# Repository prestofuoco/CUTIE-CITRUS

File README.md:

# computational imaging & telemetry for reconnaissance under suborbit
see CUTIE-CITRUS.pdf for schematics, and layout.pdf for PCB layout.

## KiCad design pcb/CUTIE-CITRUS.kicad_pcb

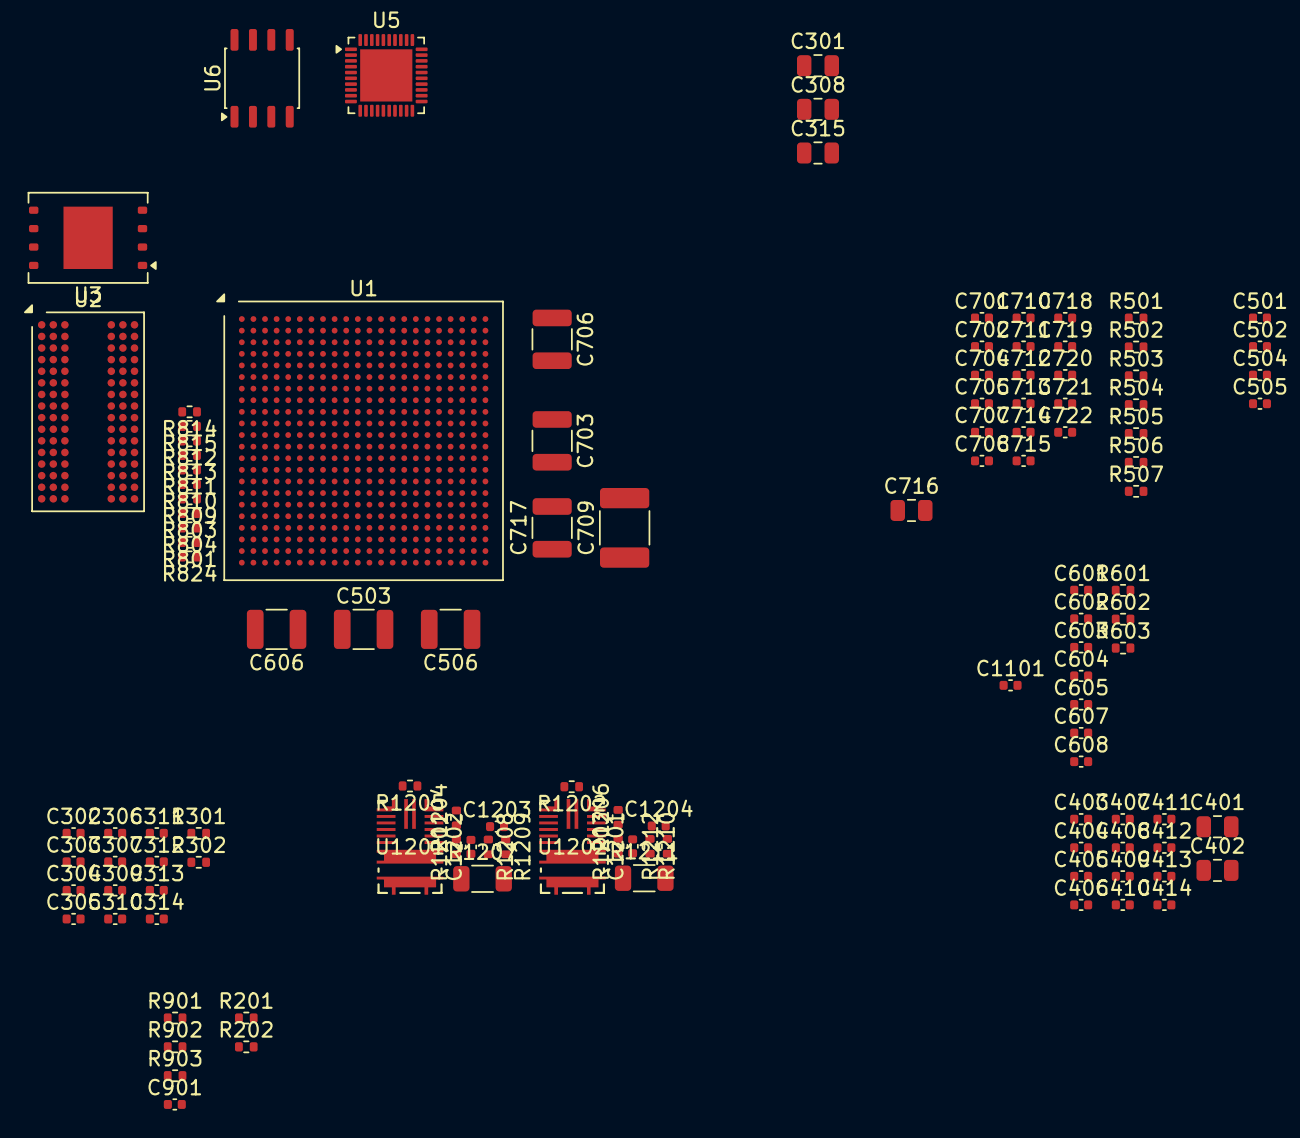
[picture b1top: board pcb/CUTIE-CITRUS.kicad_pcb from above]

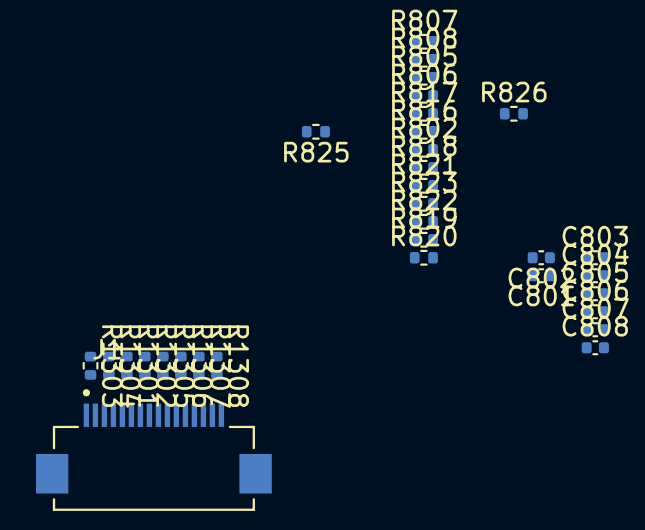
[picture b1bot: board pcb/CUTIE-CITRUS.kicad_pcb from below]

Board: 2 copper layers, 150 parts (32 on the bottom side), 142 nets, no tracks yet.

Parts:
C301, C308, C315, C401, C402, C716: 47uF; C_0805_2012Metric
C302, C303, C309, C310, C403, C404, C405, C406, C502, C505, C605, C702, C705, C710, C711, C718, C720: 4.7uF; C_0402_1005Metric
C304, C305, C306, C307, C311, C312, C313, C314, C407, C408, C409, C410, C411, C412, C413, C414, C501, C504, C601, C602, C603, C604, C701, C704, C707, C708, C712, C713, C714, C715, C719, C721, C722: 470nF; C_0402_1005Metric
C503, C506, C606, C703, C706, C717: 100uF; C_1210_3225Metric
C607, C608, C803, C804, C805, C806, C901, C1101, C1203, C1204: 0.1uF; C_0402_1005Metric
C709: 330uF; C_1812_4532Metric
C801, C802: 47nF; C_0402_1005Metric
C807: 1uF; C_0402_1005Metric
C808: 10uF; C_0402_1005Metric
C1201, C1202: 39pF; C_0402_1005Metric
J1: HIROSE_FH12-16S-0.5SH_55; HIROSE_FH12-16S-0.5SH_55_
R201, R202: 10K 1%; R_0402_1005Metric
R301, R302, R603: 4.7K; R_0402_1005Metric
R501, R1203: 20K; R_0402_1005Metric
R502, R503, R504, R505, R506, R507, R901, R902, R903, R1202, R1205: 10K; R_0402_1005Metric
R601, R602, R825: 100; R_0402_1005Metric
R801, R802, R803, R804, R805, R806, R807, R808, R809, R810, R811, R812, R813, R814, R815, R816, R817, R818, R819, R820, R821, R822, R823, R824, R1301, R1302, R1303, R1304, R1305, R1306, R1307, R1308: 22 1%; R_0402_1005Metric
R826: 240; R_0402_1005Metric
R1201: 37.4K; R_0402_1005Metric
R1204: 5.1K; R_0402_1005Metric
R1206: 30K; R_0402_1005Metric
R1207: 0.003; R_1206_3216Metric
R1208, R1209, R1210, R1212: 10; R_0402_1005Metric
R1211: 0.01; R_1206_3216Metric
U1: XC7Z020CLG484; Xilinx_CLG484_CLG485
U2: MT41K256M16; Micron_FBGA-96_7.5x13.5mm_Layout9x16_P0.8mm
U3: S25FL128SAGNFV003; WSON-8-1EP_8x6mm_P1.27mm_EP3.4x4.3mm
U5: RTL8211F-CG; QFN-40-1EP_5x5mm_P0.4mm_EP3.6x3.6mm
U6: TCAN334; JEITA_SOIC-8_3.9x4.9mm_P1.27mm
U1201, U1202: MPM3650; QFN-24_MPM3650_MNP

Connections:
/Debug Connectors/3V3_Z: J1.15, J1.16
/Debug Connectors/JTAG.TCK: R1308.1, U1.G11 (TCK_0)
/Debug Connectors/JTAG.TDI: R1306.1, U1.H13 (TDI_0)
/Debug Connectors/JTAG.TDO: R1305.1, U1.G14 (TDO_0)
/Debug Connectors/JTAG.TMS: R1307.1, U1.G12 (TMS_0)
/Debug Connectors/UART0.RX: R1304.1, U1.B6 (PS_MIO14_500)
/Debug Connectors/UART0.TX: R1303.1, U1.E6 (PS_MIO15_500)
/PHYs/3V3_Z: C1101.1, U6.3 (VCC), U6.8 (STB)
/PHYs/CAN0.RX: U1.G7 (PS_MIO10_500), U6.1 (TXD)
/PHYs/CAN0.TX: U1.B4 (PS_MIO11_500), U6.4 (RXD)
/PHYs/ETH0.MDCK: U1.D10 (PS_MIO52_501), U5.13 (MDC)
/PHYs/ETH0.MDIO: U1.C12 (PS_MIO53_501), U5.14 (MDIO)
/PHYs/ETH0.RX_CLK: U1.A14 (PS_MIO22_501), U5.27 (RXC)
/PHYs/ETH0.RX_CTL: U1.D7 (PS_MIO27_501), U5.26 (RXCTL)
/PHYs/ETH0.RX_D0: U1.E11 (PS_MIO23_501), U5.25 (RXD0)
/PHYs/ETH0.RX_D1: U1.B7 (PS_MIO24_501), U5.24 (RXD1)
/PHYs/ETH0.RX_D2: U1.F12 (PS_MIO25_501), U5.23 (RXD2)
/PHYs/ETH0.RX_D3: U1.A13 (PS_MIO26_501), U5.22 (RXD3)
/PHYs/ETH0.TX_CLK: U1.D6 (PS_MIO16_501), U5.20 (TXC)
/PHYs/ETH0.TX_CTL: U1.F11 (PS_MIO21_501), U5.19 (TXCTL)
/PHYs/ETH0.TX_D0: U1.E9 (PS_MIO17_501), U5.18 (TXD0)
/PHYs/ETH0.TX_D1: U1.A7 (PS_MIO18_501), U5.17 (TXD1)
/PHYs/ETH0.TX_D2: U1.E10 (PS_MIO19_501), U5.16 (TXD2)
/PHYs/ETH0.TX_D3: U1.A8 (PS_MIO20_501), U5.15 (TXD3)
/Power Supply/1V0: R1211.2, R1212.2
/Power Supply/1V0_P: C1201.1, R1203.1, R1210.2, R1211.1, U1202.9 (OUT), U1202.10 (OUT), U1202.11 (OUT), U1202.12 (OUT)
/Power Supply/1V0_PG: R1202.1, U1202.20 (PG), U1202.21 (PG)
/Power Supply/1V0_SENS_N: C1204.2, R1212.1
/Power Supply/1V0_SENS_P: C1204.1, R1210.1
/Power Supply/5V0: R1207.2, R1209.2, U1202.22 (VIN)
/Power Supply/5V0_P: C1202.1, R1201.1, R1207.1, R1208.2, U1201.9 (OUT), U1201.10 (OUT), U1201.11 (OUT), U1201.12 (OUT)
/Power Supply/5V0_PG: R1205.1, U1201.20 (PG), U1201.21 (PG), U1202.16 (EN)
/Power Supply/5V0_SENS_N: C1203.2, R1209.1
/Power Supply/5V0_SENS_P: C1203.1, R1208.1
/Power Supply/VBUS: U1201.16 (EN), U1201.22 (VIN)
/SoC/1V8_Z: C704.2, C705.2, C706.2, C716.2, C720.2, C721.2, C722.2, U1.A10 (VCCO_MIO1_501), U1.B13 (VCCO_MIO1_501), U1.D9 (VCCO_MIO1_501), U1.E12 (VCCO_MIO1_501), U1.K9 (VCCPAUX), U1.K11 (VCCADC_0), U1.L10 (VCCAUX), U1.M9 (VCCPAUX), U1.N10 (VCCAUX), U1.P9 (VCCPAUX), U1.P11 (VCCAUX), U1.R10 (VCCAUX), U1.T9 (VCCPAUX)
/SoC/1V35_DDR: C606.2, C803.2, C804.2, C805.2, C806.2, C807.2, C808.2, R201.1, R601.1, U1.E2 (VCCO_DDR_502), U1.F5 (VCCO_DDR_502), U1.H1 (VCCO_DDR_502), U1.J4 (VCCO_DDR_502), U1.K7 (VCCO_DDR_502), U1.M3 (VCCO_DDR_502), U1.N6 (VCCO_DDR_502), U1.R2 (VCCO_DDR_502), U1.V1 (VCCO_DDR_502), U2.A1 (V_{DDQ}), U2.A8 (V_{DDQ}), U2.B2 (V_{DD}), U2.C1 (V_{DDQ}), U2.C9 (V_{DDQ}), U2.D2 (V_{DDQ}), U2.D9 (V_{DD}), U2.E9 (V_{DDQ}), U2.F1 (V_{DDQ}), U2.G7 (V_{DD}), U2.H2 (V_{DDQ}), U2.H9 (V_{DDQ}), U2.K2 (V_{DD}), U2.K8 (V_{DD}), U2.N1 (V_{DD}), U2.N9 (V_{DD}), U2.R1 (V_{DD}), U2.R9 (V_{DD})
/SoC/2V5_Z: C301.2, C302.2, C303.2, C304.2, C305.2, C306.2, C307.2, U1.AA10 (VCCO_13), U1.AB3 (VCCO_13), U1.T5 (VCCO_13), U1.U8 (VCCO_13), U1.V11 (VCCO_13), U1.W4 (VCCO_13), U1.Y7 (VCCO_13)
/SoC/3V3_Z: C308.2, C309.2, C310.2, C311.2, C312.2, C313.2, C314.2, C315.2, C501.2, C502.2, C503.2, R301.1, R302.1, R501.1, R502.1, R503.2, U1.AA20 (VCCO_33), U1.AB13 (VCCO_33), U1.B3 (VCCO_MIO0_500), U1.C6 (VCCO_MIO0_500), U1.R12 (VCCO_0), U1.T7 (RSVDVCC1), U1.T8 (RSVDVCC2), U1.T10 (RSVDVCC3), U1.T13 (CFGBVS_0), U1.U18 (VCCO_33), U1.V21 (VCCO_33), U1.W14 (VCCO_33), U1.Y17 (VCCO_33)
/SoC/DRAM/0V675_REF: C801.2, C802.2, R201.2, R202.1, U1.H7 (PS_DDR_VREF0_502), U1.P7 (PS_DDR_VREF1_502), U2.H1 (V_{REFDQ}), U2.M8 (V_{REFCA})
/SoC/DRAM/DDR_A0: R801.1, U1.M4 (PS_DDR_A0_502)
/SoC/DRAM/DDR_A0_T: R801.2, U2.N3 (A0)
/SoC/DRAM/DDR_A1: R802.1, U1.M5 (PS_DDR_A1_502)
/SoC/DRAM/DDR_A1_T: R802.2, U2.P7 (A1)
/SoC/DRAM/DDR_A2: R803.1, U1.K4 (PS_DDR_A2_502)
/SoC/DRAM/DDR_A2_T: R803.2, U2.P3 (A2)
/SoC/DRAM/DDR_A3: R804.1, U1.L4 (PS_DDR_A3_502)
/SoC/DRAM/DDR_A3_T: R804.2, U2.N2 (A3)
/SoC/DRAM/DDR_A4: R805.1, U1.K6 (PS_DDR_A4_502)
/SoC/DRAM/DDR_A4_T: R805.2, U2.P8 (A4)
/SoC/DRAM/DDR_A5: R806.1, U1.K5 (PS_DDR_A5_502)
/SoC/DRAM/DDR_A5_T: R806.2, U2.P2 (A5)
/SoC/DRAM/DDR_A6: R807.1, U1.J7 (PS_DDR_A6_502)
/SoC/DRAM/DDR_A6_T: R807.2, U2.R8 (A6)
/SoC/DRAM/DDR_A7: R808.1, U1.J6 (PS_DDR_A7_502)
/SoC/DRAM/DDR_A7_T: R808.2, U2.R2 (A7)
/SoC/DRAM/DDR_A8: R809.1, U1.J5 (PS_DDR_A8_502)
/SoC/DRAM/DDR_A8_T: R809.2, U2.T8 (A8)
/SoC/DRAM/DDR_A9: R810.1, U1.H5 (PS_DDR_A9_502)
/SoC/DRAM/DDR_A9_T: R810.2, U2.R3 (A9)
/SoC/DRAM/DDR_A10: R811.1, U1.J3 (PS_DDR_A10_502)
/SoC/DRAM/DDR_A10_T: R811.2, U2.L7 (A10/AP)
/SoC/DRAM/DDR_A11: R812.1, U1.G5 (PS_DDR_A11_502)
/SoC/DRAM/DDR_A11_T: R812.2, U2.R7 (A11)
/SoC/DRAM/DDR_A12: R813.1, U1.H4 (PS_DDR_A12_502)
/SoC/DRAM/DDR_A12_T: R813.2, U2.N7 (A12/~BC)
/SoC/DRAM/DDR_A13: R814.1, U1.F4 (PS_DDR_A13_502)
/SoC/DRAM/DDR_A13_T: R814.2, U2.T3 (A13)
/SoC/DRAM/DDR_A14: R815.1, U1.G4 (PS_DDR_A14_502)
/SoC/DRAM/DDR_A14_T: R815.2, U2.T7 (A14)
/SoC/DRAM/DDR_BA0: R816.1, U1.L7 (PS_DDR_BA0_502)
/SoC/DRAM/DDR_BA0_T: R816.2, U2.M2 (BA0)
/SoC/DRAM/DDR_BA1: R817.1, U1.L6 (PS_DDR_BA1_502)
/SoC/DRAM/DDR_BA1_T: R817.2, U2.N8 (BA1)
/SoC/DRAM/DDR_BA2: R818.1, U1.M6 (PS_DDR_BA2_502)
/SoC/DRAM/DDR_BA2_T: R818.2, U2.M3 (BA2)
/SoC/DRAM/DDR_CAS: R821.1, U1.P3 (PS_DDR_CAS_B_502)
/SoC/DRAM/DDR_CAS_T: R821.2, U2.K3 (~CAS)
/SoC/DRAM/DDR_CKE: R824.1, U1.V3 (PS_DDR_CKE_502)
/SoC/DRAM/DDR_CKE_T: R824.2, U2.K9 (CKE)
/SoC/DRAM/DDR_CK_N: R825.2, U1.N5 (PS_DDR_CKN_502), U2.K7 (~CK)
/SoC/DRAM/DDR_CK_P: R825.1, U1.N4 (PS_DDR_CKP_502), U2.J7 (CK)
/SoC/DRAM/DDR_CS: R819.1, U1.P6 (PS_DDR_CS_B_502)
/SoC/DRAM/DDR_CS_T: R819.2, U2.L2 (~CS)
/SoC/DRAM/DDR_DM0: U1.H3 (PS_DDR_DM1_502), U2.E7 (LDM)
/SoC/DRAM/DDR_DM1: U1.B1 (PS_DDR_DM0_502), U2.D3 (UDM)
/SoC/DRAM/DDR_DQ0: U1.G2 (PS_DDR_DQ8_502), U2.E3 (DQ0)
/SoC/DRAM/DDR_DQ1: U1.G1 (PS_DDR_DQ9_502), U2.F7 (DQ1)
/SoC/DRAM/DDR_DQ2: U1.L1 (PS_DDR_DQ10_502), U2.F2 (DQ2)
/SoC/DRAM/DDR_DQ3: U1.L2 (PS_DDR_DQ11_502), U2.F8 (DQ3)
/SoC/DRAM/DDR_DQ4: U1.L3 (PS_DDR_DQ12_502), U2.H3 (DQ4)
/SoC/DRAM/DDR_DQ5: U1.K1 (PS_DDR_DQ13_502), U2.H8 (DQ5)
/SoC/DRAM/DDR_DQ6: U1.J1 (PS_DDR_DQ14_502), U2.G2 (DQ6)
/SoC/DRAM/DDR_DQ7: U1.K3 (PS_DDR_DQ15_502), U2.H7 (DQ7)
/SoC/DRAM/DDR_DQ8: U1.D1 (PS_DDR_DQ0_502), U2.D7 (DQ8)
/SoC/DRAM/DDR_DQ9: U1.C3 (PS_DDR_DQ1_502), U2.C3 (DQ9)
/SoC/DRAM/DDR_DQ10: U1.B2 (PS_DDR_DQ2_502), U2.C8 (DQ10)
/SoC/DRAM/DDR_DQ11: U1.D3 (PS_DDR_DQ3_502), U2.C2 (DQ11)
/SoC/DRAM/DDR_DQ12: U1.E3 (PS_DDR_DQ4_502), U2.A7 (DQ12)
/SoC/DRAM/DDR_DQ13: U1.E1 (PS_DDR_DQ5_502), U2.A2 (DQ13)
/SoC/DRAM/DDR_DQ14: U1.F2 (PS_DDR_DQ6_502), U2.B8 (DQ14)
/SoC/DRAM/DDR_DQ15: U1.F1 (PS_DDR_DQ7_502), U2.A3 (DQ15)
/SoC/DRAM/DDR_DQS_0_N: U1.J2 (PS_DDR_DQS_N1_502), U2.G3 (~LDQS)
/SoC/DRAM/DDR_DQS_0_P: U1.H2 (PS_DDR_DQS_P1_502), U2.F3 (LDQS)
/SoC/DRAM/DDR_DQS_1_N: U1.D2 (PS_DDR_DQS_N0_502), U2.B7 (~UDQS)
/SoC/DRAM/DDR_DQS_1_P: U1.C2 (PS_DDR_DQS_P0_502), U2.C7 (UDQS)
/SoC/DRAM/DDR_DRST: R603.1, U1.F3 (PS_DDR_DRST_B_502), U2.T2 (~RESET)
/SoC/DRAM/DDR_ODT: R823.1, U1.P5 (PS_DDR_ODT_502)
/SoC/DRAM/DDR_ODT_T: R823.2, U2.K1 (ODT)
/SoC/DRAM/DDR_RAS: R820.1, U1.R5 (PS_DDR_RAS_B_502)
/SoC/DRAM/DDR_RAS_T: R820.2, U2.J3 (~RAS)
/SoC/DRAM/DDR_WE: R822.1, U1.R4 (PS_DDR_WE_B_502)
/SoC/DRAM/DDR_WE_T: R822.2, U2.L3 (~WE)
/SoC/DRAM/DDR_ZQ: R826.1, U2.L8 (ZQ)
/SoC/FPGA 0, 13, 33/INIT_B: R302.2, U1.T14 (INIT_B_0)
/SoC/FPGA 0, 13, 33/PROGRAM_B: R301.2, U1.T11 (PROGRAM_B_0)
/SoC/Flash Memory/3V3_Z: C901.2, R901.1, R902.1, R903.1, U3.8 (VCC)
/SoC/Flash Memory/QSPI0.CS0: R903.2, U1.A1 (PS_MIO1_500), U3.1 (CS#)
/SoC/Flash Memory/QSPI0.IO1: U1.A2 (PS_MIO2_500), U3.2 (SO/IO1)
/SoC/Flash Memory/QSPI0.IO2: R902.2, U1.F6 (PS_MIO3_500), U3.3 (WP#/IO2)
/SoC/Flash Memory/QSPI0.IO3: R505.1, R901.2, U1.E4 (PS_MIO4_500), U3.7 (HOLD#/IO3)
/SoC/Flash Memory/QSPI0.SCLK: U1.A4 (PS_MIO6_500), U3.6 (SCK)
/SoC/SoC 500, 501/MIO7: R504.1, U1.D5 (PS_MIO7_500)
/SoC/SoC 500, 501/MIO8: R502.2, U1.E5 (PS_MIO8_500)
/SoC/SoC 500, 501/QSPI0.IO4: R501.2, U1.A3 (PS_MIO5_500)
/SoC/SoC 502/DDR_VRN: R602.1, U1.M7 (PS_DDR_VRN_502)
/SoC/SoC 502/DDR_VRP: R601.2, U1.N7 (PS_DDR_VRP_502)
/SoC/SoC Power/1V0_Z: C701.2, C707.2, C708.2, C709.2, C711.2, C712.2, C713.2, C714.2, C715.2, C719.2, U1.G8 (VCCPINT), U1.H9 (VCCPINT), U1.H11 (VCCBRAM), U1.J8 (VCCPINT), U1.J10 (VCCBRAM), U1.J12 (VCCINT), U1.J14 (VCCINT), U1.K13 (VCCINT), U1.L8 (VCCPINT), U1.L14 (VCCINT), U1.M13 (VCCINT), U1.N8 (VCCPINT), U1.N14 (VCCINT), U1.P13 (VCCINT), U1.R8 (VCCPINT), U1.R14 (VCCINT)
GND: C301.1, C302.1, C303.1, C304.1, C305.1, C306.1, C307.1, C308.1, C309.1, C310.1, C311.1, C312.1, C313.1, C314.1, C315.1, C401.1, C402.1, C403.1, C404.1, C405.1, C406.1, C407.1, C408.1, C409.1, C410.1, C411.1, C412.1, C413.1, C414.1, C501.1, C502.1, C503.1, C504.1, C505.1, C506.1, C601.1, C602.1, C603.1, C604.1, C605.1, C606.1, C607.1, C608.1, C701.1, C702.1, C703.1, C704.1, C705.1, C706.1, C707.1, C708.1, C709.1, C710.1, C711.1, C712.1, C713.1, C714.1, C715.1, C716.1, C717.1, C718.1, C719.1, C720.1, C721.1, C722.1, C801.1, C802.1, C803.1, C804.1, C805.1, C806.1, C807.1, C808.1, C901.1, C1101.2, J1.3, J1.4, J1.7, J1.8, J1.13, J1.14, R202.2, R504.2, R505.2, R506.2, R507.2, R602.2, R603.2, R1202.2, R1204.2, R1205.2, R1206.2, U1.A5 (GND), U1.A15 (GND), U1.AA5 (GND), U1.AA15 (GND), U1.AB8 (GND), U1.AB18 (GND), U1.B8 (GND), U1.B18 (GND), U1.C1 (GND), U1.C11 (GND), U1.C21 (GND), U1.D4 (GND), U1.D14 (GND), U1.E7 (GND), U1.E17 (GND), U1.F10 (GND), U1.F20 (GND), U1.G3 (GND), U1.G9 (VCCBATT_0), U1.G10 (RSVDGND), U1.H6 (GND), U1.H8 (GND), U1.H12 (GND), U1.H14 (GND), U1.H16 (GND), U1.J9 (GND), U1.J11 (GND), U1.J13 (GND), U1.J19 (GND), U1.K2 (GND), U1.K8 (GND), U1.K10 (GND), U1.K12 (GNDADC_0), U1.K14 (GND), U1.K22 (GND), U1.L5 (GND), U1.L9 (GND), U1.L11 (VP_0), U1.L12 (VREFN_0), U1.L13 (GND), U1.L15 (GND), U1.M8 (GND), U1.M10 (GND), U1.M11 (VREFP_0), U1.M12 (VN_0), U1.M14 (GND), U1.M18 (GND), U1.N1 (GND), U1.N9 (GND), U1.N11 (DXP_0), U1.N12 (DXN_0), U1.N13 (GND), U1.N21 (GND), U1.P4 (GND), U1.P8 (GND), U1.P10 (GND), U1.P12 (GND), U1.P14 (GND), U1.R9 (GND), U1.R11 (GND), U1.R13 (GND), U1.R17 (GND), U1.T20 (GND), U1.U3 (GND), U1.U13 (GND), U1.V6 (GND), U1.V16 (GND), U1.W9 (GND), U1.W19 (GND), U1.Y2 (GND), U1.Y12 (GND), U1.Y22 (GND), U2.A9 (V_{SS}), U2.B1 (V_{SSQ}), U2.B3 (V_{SS}), U2.B9 (V_{SSQ}), U2.D1 (V_{SSQ}), U2.D8 (V_{SSQ}), U2.E1 (V_{SS}), U2.E2 (V_{SSQ}), U2.E8 (V_{SSQ}), U2.F9 (V_{SSQ}), U2.G1 (V_{SSQ}), U2.G8 (V_{SS}), U2.G9 (V_{SSQ}), U2.J2 (V_{SS}), U2.J8 (V_{SS}), U2.M1 (V_{SS}), U2.M9 (V_{SS}), U2.P1 (V_{SS}), U2.P9 (V_{SS}), U2.T1 (V_{SS}), U2.T9 (V_{SS}), U3.4 (VSS), U3.9 (EP), U5.41 (GND), U6.2 (GND), U6.5 (SHDN), U1201.1 (PGND), U1201.2 (PGND), U1201.3 (PGND), U1201.4 (PGND), U1201.5 (PGND), U1201.6 (VCC), U1201.18 (AGND), U1201.24 (PGND), U1202.1 (PGND), U1202.2 (PGND), U1202.3 (PGND), U1202.4 (PGND), U1202.5 (PGND), U1202.6 (VCC), U1202.18 (AGND), U1202.24 (PGND)
unnamed: C401.2, C403.2, C405.2, C407.2, C409.2, C411.2, C413.2
unnamed: C402.2, C404.2, C406.2, C408.2, C410.2, C412.2, C414.2
unnamed: J1.1, R1303.2
unnamed: J1.2, R1304.2
unnamed: J1.5, R1301.2
unnamed: J1.6, R1302.2
unnamed: J1.9, R1305.2
unnamed: J1.10, R1306.2
unnamed: J1.11, R1307.2
unnamed: J1.12, R1308.2
unnamed: R503.1, U1.B5 (PS_POR_B_500)
unnamed: C1202.2, R1201.2, R1204.1, U1201.17 (FB)
unnamed: C1201.2, R1203.2, R1206.1, U1202.17 (FB)

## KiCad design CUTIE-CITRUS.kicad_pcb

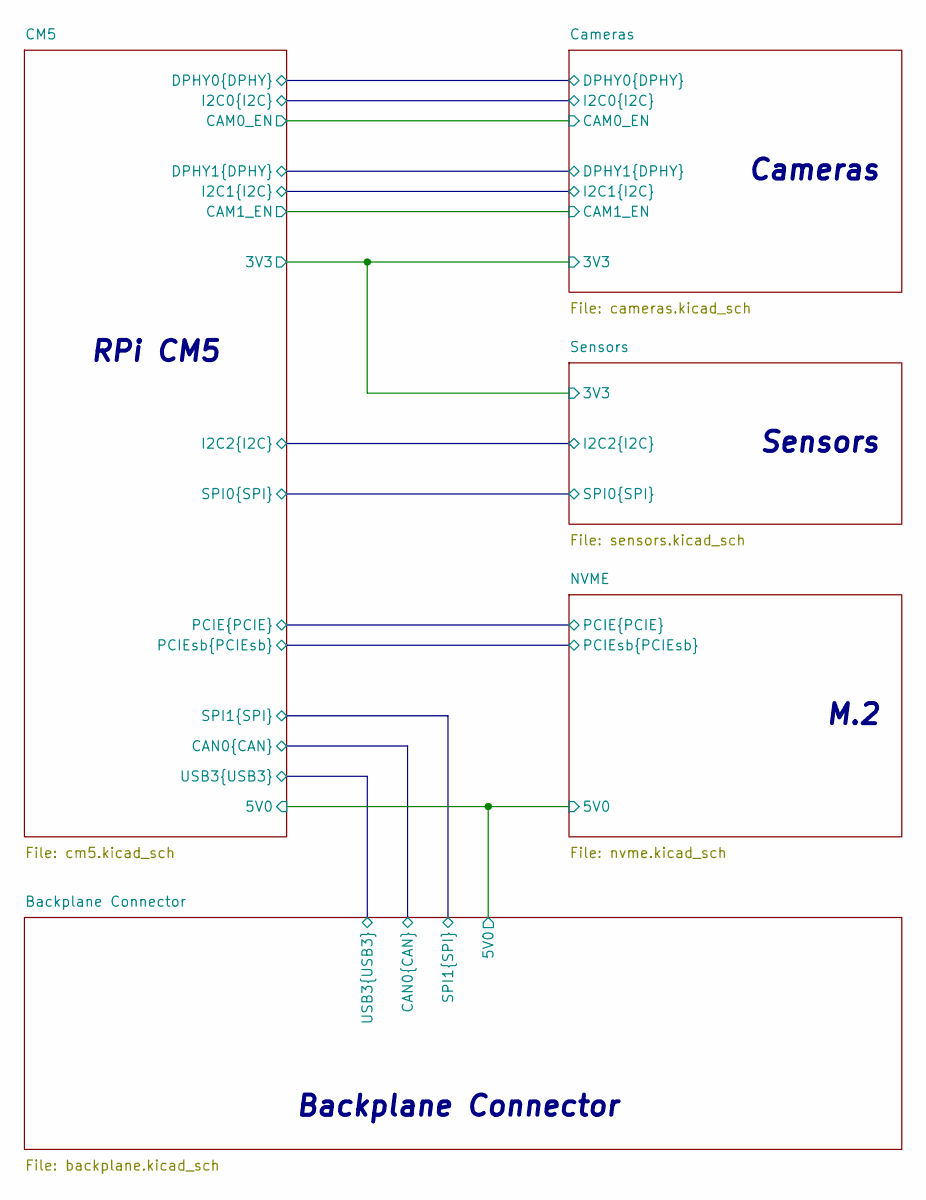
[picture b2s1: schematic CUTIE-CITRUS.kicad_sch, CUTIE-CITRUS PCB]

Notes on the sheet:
Cameras
Backplane Connector
Sensors
M.2
RPi CM5

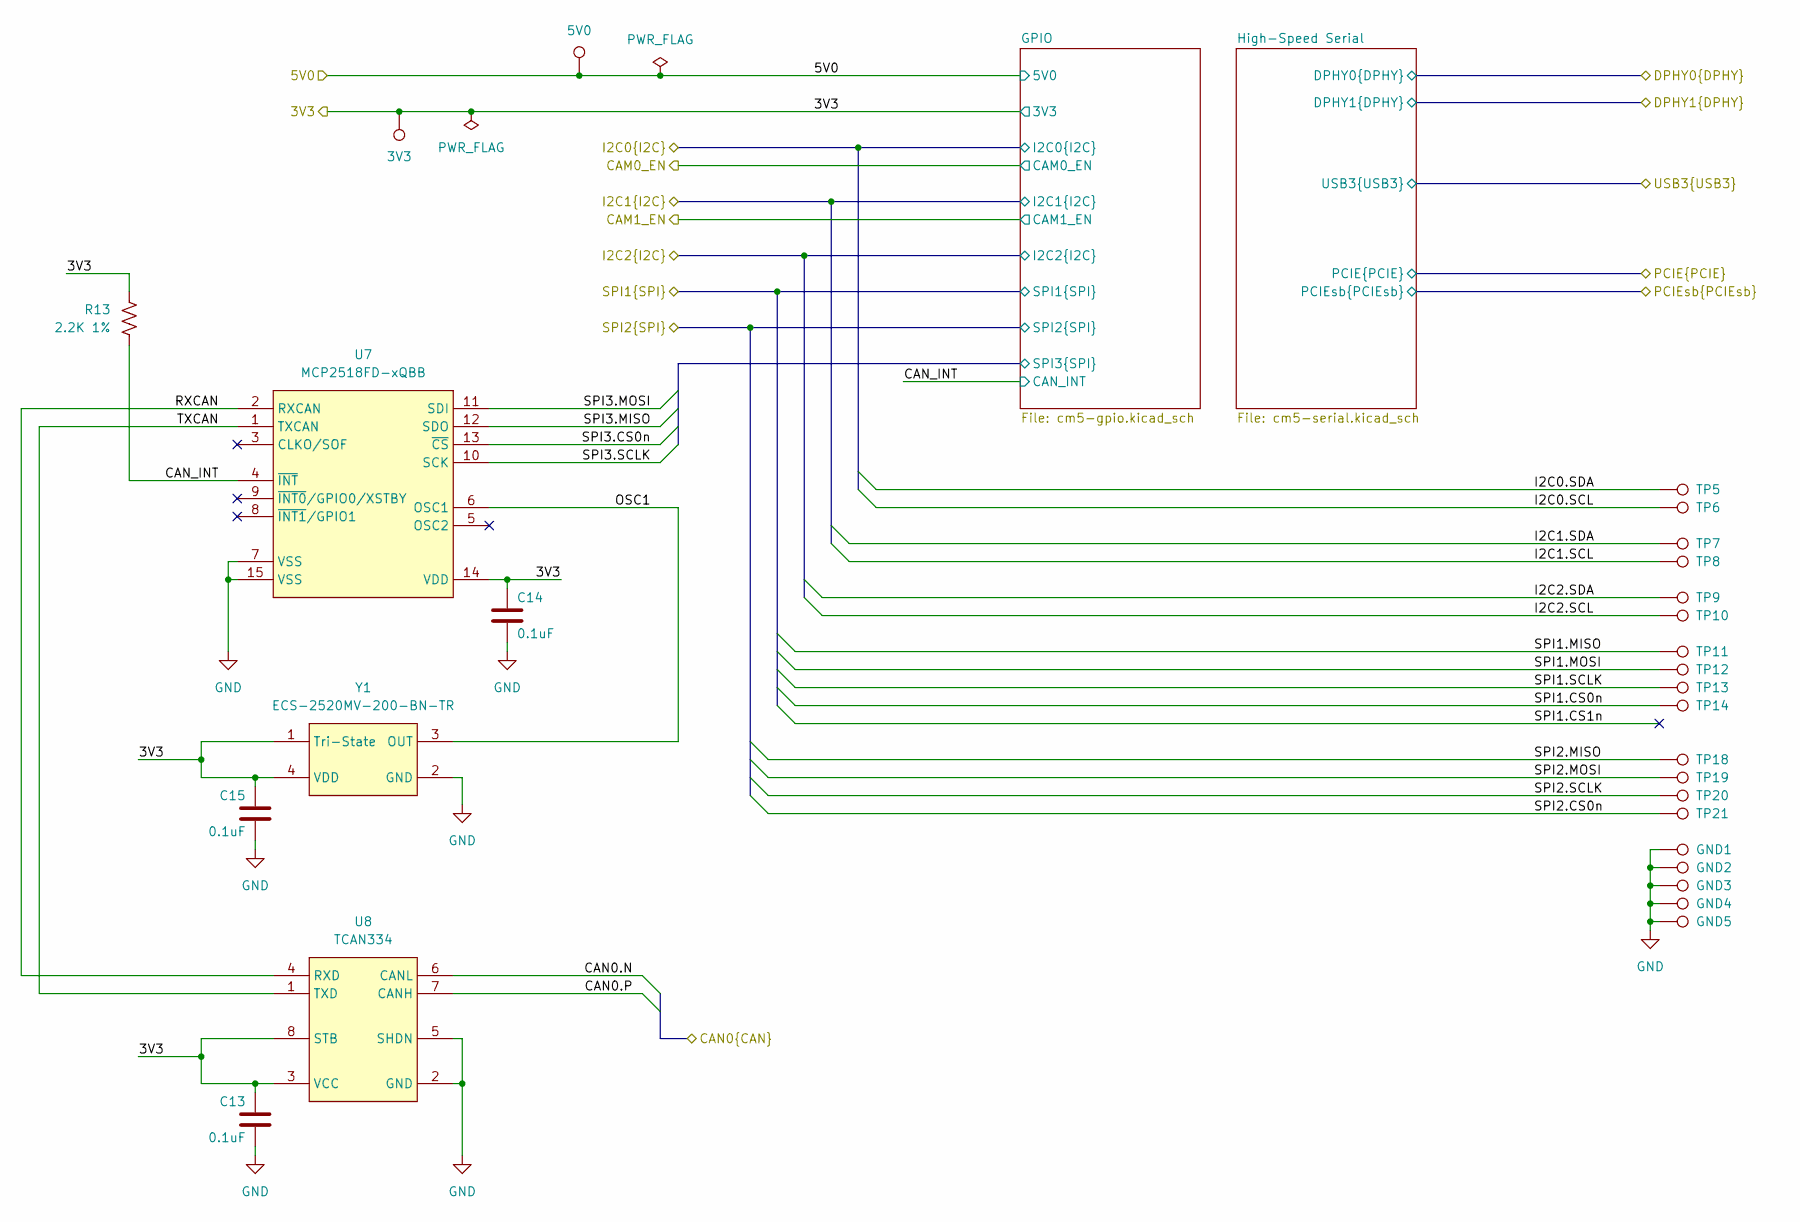
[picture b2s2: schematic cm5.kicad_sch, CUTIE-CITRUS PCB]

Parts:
3V3, 5V0: TestPoint; TestPoint_Pad_D2.0mm
C13, C14, C15: 0.1uF; C_0402_1005Metric; Part Description 0.1uF 10% 16V Ceramic Capacitor X7R 040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
GND1, GND2, GND3, GND4, GND5: TestPoint; TestPoint_Pad_D1.0mm
R13: 2.2K 1%; R_0402_1005Metric; Part Description Resistor 2.2K M1005 1% 63mW
TP5, TP6, TP7, TP8, TP9, TP10, TP11, TP12, TP13, TP14, TP18, TP19, TP20, TP21: TestPoint; TestPoint_Pad_D1.0mm
U7: MCP2518FD-xQBB; DFN-14-1EP_3x4.5mm_P0.65mm_EP1.65x4.25mm
U8: TCAN334; JEITA_SOIC-8_3.9x4.9mm_P1.27mm
Y1: ECS-2520MV-200-BN-TR; Oscillator_SMD_ECS_2520MV-xxx-xx-4Pin_2.5x2.0mm

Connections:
/Backplane Connector/5V0: 5V0.1; also elsewhere on the board
/Backplane Connector/CAN0.N: U8.6 (CANL); also elsewhere on the board
/Backplane Connector/CAN0.P: U8.7 (CANH); also elsewhere on the board
/Backplane Connector/SPI2.CS0n: TP21.1; also elsewhere on the board
/Backplane Connector/SPI2.MISO: TP18.1; also elsewhere on the board
/Backplane Connector/SPI2.MOSI: TP19.1; also elsewhere on the board
/Backplane Connector/SPI2.SCLK: TP20.1; also elsewhere on the board
/CM5/3V3: 3V3.1, C13.1, C14.1, C15.1, R13.1, U7.14 (VDD), U8.3 (VCC), U8.8 (STB), Y1.1 (Tri-State), Y1.4 (VDD); also elsewhere on the board
/CM5/CAN_INT: R13.2, U7.4 (~INT); also elsewhere on the board
/CM5/GPIO/SPI3.CS0n: U7.13 (~CS); also elsewhere on the board
/CM5/GPIO/SPI3.MISO: U7.12 (SDO); also elsewhere on the board
/CM5/GPIO/SPI3.MOSI: U7.11 (SDI); also elsewhere on the board
/CM5/GPIO/SPI3.SCLK: U7.10 (SCK); also elsewhere on the board
/CM5/I2C0.SCL: TP6.1; also elsewhere on the board
/CM5/I2C0.SDA: TP5.1; also elsewhere on the board
/CM5/I2C1.SCL: TP8.1; also elsewhere on the board
/CM5/I2C1.SDA: TP7.1; also elsewhere on the board
/CM5/I2C2.SCL: TP10.1; also elsewhere on the board
/CM5/I2C2.SDA: TP9.1; also elsewhere on the board
/CM5/OSC1: U7.6 (OSC1), Y1.3 (OUT)
/CM5/RXCAN: U7.2 (RXCAN), U8.4 (RXD)
/CM5/SPI1.CS0n: TP14.1; also elsewhere on the board
/CM5/SPI1.MISO: TP11.1; also elsewhere on the board
/CM5/SPI1.MOSI: TP12.1; also elsewhere on the board
/CM5/SPI1.SCLK: TP13.1; also elsewhere on the board
/CM5/TXCAN: U7.1 (TXCAN), U8.1 (TXD)
GND: C13.2, C14.2, C15.2, GND1.1, GND2.1, GND3.1, GND4.1, GND5.1, U7.7 (VSS), U7.15 (VSS), U8.2 (GND), U8.5 (SHDN), Y1.2 (GND); also elsewhere on the board

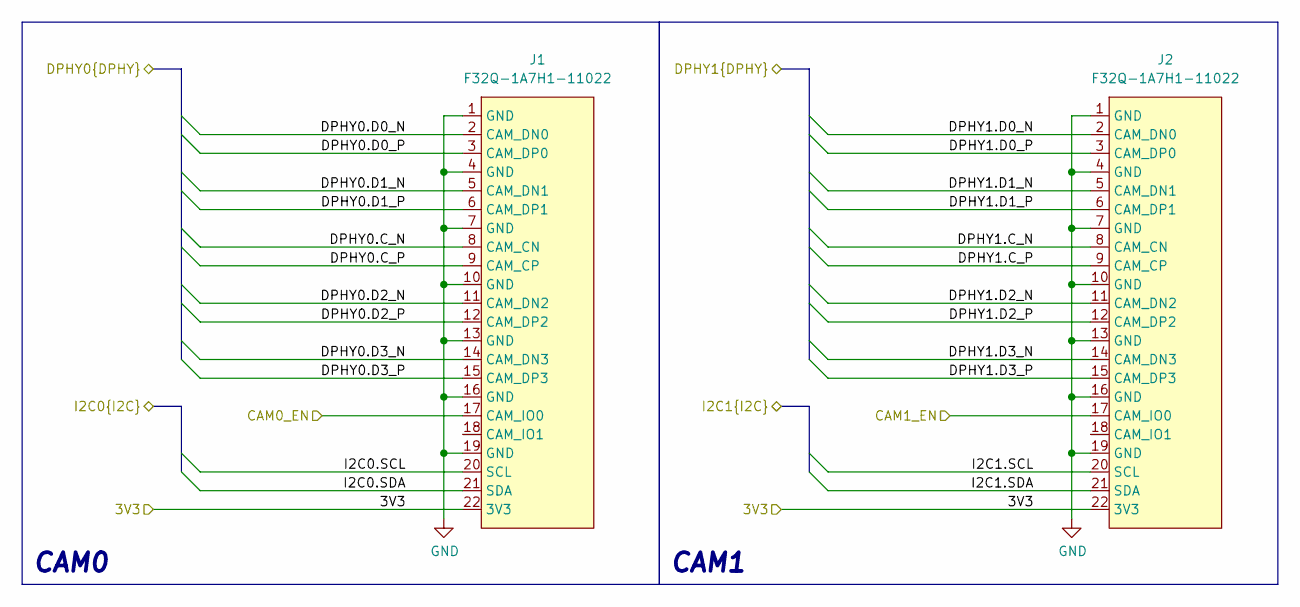
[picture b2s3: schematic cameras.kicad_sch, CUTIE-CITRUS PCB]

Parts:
J1, J2: F32Q-1A7H1-11022; Hirose_FH12-22S-0.5SH_1x22-1MP_P0.50mm_Horizontal

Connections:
/CM5/3V3: J1.22 (3V3), J2.22 (3V3); also elsewhere on the board
/CM5/CAM0_EN: J1.17 (CAM_IO0); also elsewhere on the board
/CM5/CAM1_EN: J2.17 (CAM_IO0); also elsewhere on the board
/CM5/DPHY0.C_N: J1.8 (CAM_CN); also elsewhere on the board
/CM5/DPHY0.C_P: J1.9 (CAM_CP); also elsewhere on the board
/CM5/DPHY0.D0_N: J1.2 (CAM_DN0); also elsewhere on the board
/CM5/DPHY0.D0_P: J1.3 (CAM_DP0); also elsewhere on the board
/CM5/DPHY0.D1_N: J1.5 (CAM_DN1); also elsewhere on the board
/CM5/DPHY0.D1_P: J1.6 (CAM_DP1); also elsewhere on the board
/CM5/DPHY0.D2_N: J1.11 (CAM_DN2); also elsewhere on the board
/CM5/DPHY0.D2_P: J1.12 (CAM_DP2); also elsewhere on the board
/CM5/DPHY0.D3_N: J1.14 (CAM_DN3); also elsewhere on the board
/CM5/DPHY0.D3_P: J1.15 (CAM_DP3); also elsewhere on the board
/CM5/DPHY1.C_N: J2.8 (CAM_CN); also elsewhere on the board
/CM5/DPHY1.C_P: J2.9 (CAM_CP); also elsewhere on the board
/CM5/DPHY1.D0_N: J2.2 (CAM_DN0); also elsewhere on the board
/CM5/DPHY1.D0_P: J2.3 (CAM_DP0); also elsewhere on the board
/CM5/DPHY1.D1_N: J2.5 (CAM_DN1); also elsewhere on the board
/CM5/DPHY1.D1_P: J2.6 (CAM_DP1); also elsewhere on the board
/CM5/DPHY1.D2_N: J2.11 (CAM_DN2); also elsewhere on the board
/CM5/DPHY1.D2_P: J2.12 (CAM_DP2); also elsewhere on the board
/CM5/DPHY1.D3_N: J2.14 (CAM_DN3); also elsewhere on the board
/CM5/DPHY1.D3_P: J2.15 (CAM_DP3); also elsewhere on the board
/CM5/I2C0.SCL: J1.20 (SCL); also elsewhere on the board
/CM5/I2C0.SDA: J1.21 (SDA); also elsewhere on the board
/CM5/I2C1.SCL: J2.20 (SCL); also elsewhere on the board
/CM5/I2C1.SDA: J2.21 (SDA); also elsewhere on the board
GND: J1.1 (GND), J1.4 (GND), J1.7 (GND), J1.10 (GND), J1.13 (GND), J1.16 (GND), J1.19 (GND), J2.1 (GND), J2.4 (GND), J2.7 (GND), J2.10 (GND), J2.13 (GND), J2.16 (GND), J2.19 (GND); also elsewhere on the board

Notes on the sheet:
CAM1
CAM0

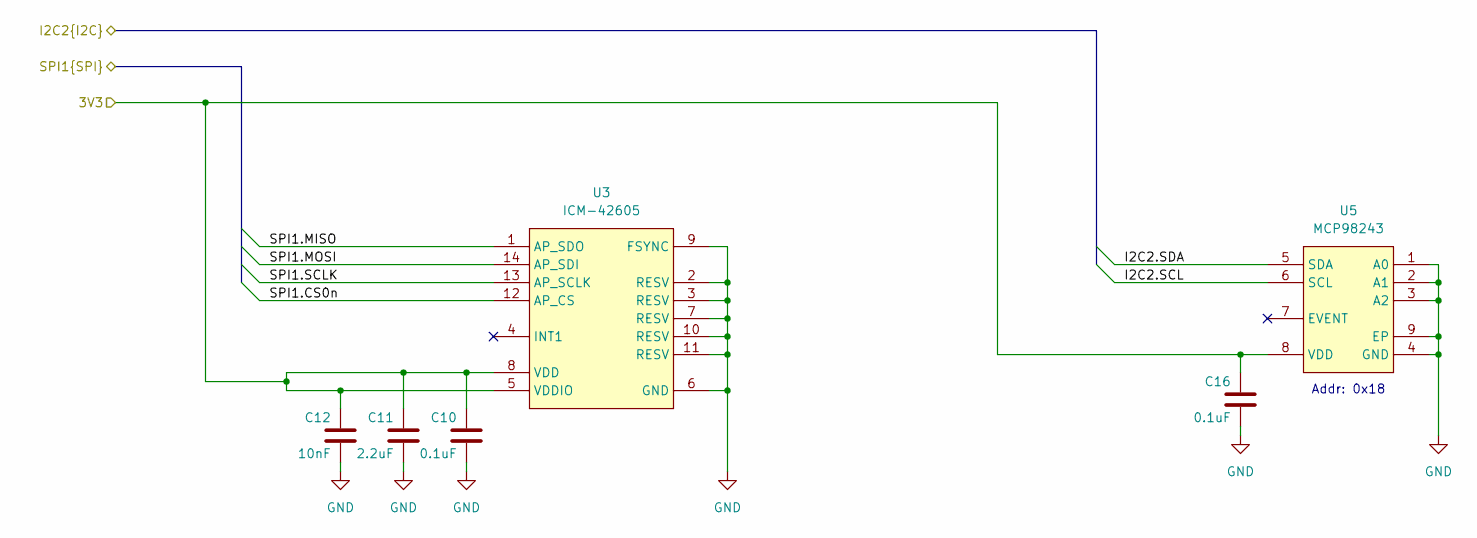
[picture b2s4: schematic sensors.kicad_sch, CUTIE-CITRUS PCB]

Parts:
C10, C16: 0.1uF; C_0402_1005Metric
C11: 2.2uF; C_0402_1005Metric; Part Description 4.7nF capacitor 0402
C12: 10nF; C_0402_1005Metric; Part Description 4.7nF capacitor 0402
U3: ICM-42605; LGA-14_3x2.5mm_P0.5mm_LayoutBorder3x4y
U5: MCP98243; DFN-8-1EP_3x2mm_P0.5mm_EP1.3x1.5mm

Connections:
/CM5/3V3: C10.1, C11.1, C12.1, C16.1, U3.5 (VDDIO), U3.8 (VDD), U5.8 (VDD); also elsewhere on the board
/CM5/I2C2.SCL: U5.6 (SCL); also elsewhere on the board
/CM5/I2C2.SDA: U5.5 (SDA); also elsewhere on the board
/CM5/SPI1.CS0n: U3.12 (AP_CS); also elsewhere on the board
/CM5/SPI1.MISO: U3.1 (AP_SDO); also elsewhere on the board
/CM5/SPI1.MOSI: U3.14 (AP_SDI); also elsewhere on the board
/CM5/SPI1.SCLK: U3.13 (AP_SCLK); also elsewhere on the board
GND: C10.2, C11.2, C12.2, C16.2, U3.2 (RESV), U3.3 (RESV), U3.6 (GND), U3.7 (RESV), U3.9 (FSYNC), U3.10 (RESV), U3.11 (RESV), U5.1 (A0), U5.2 (A1), U5.3 (A2), U5.4 (GND), U5.9 (EP); also elsewhere on the board

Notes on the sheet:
Addr: 0x18

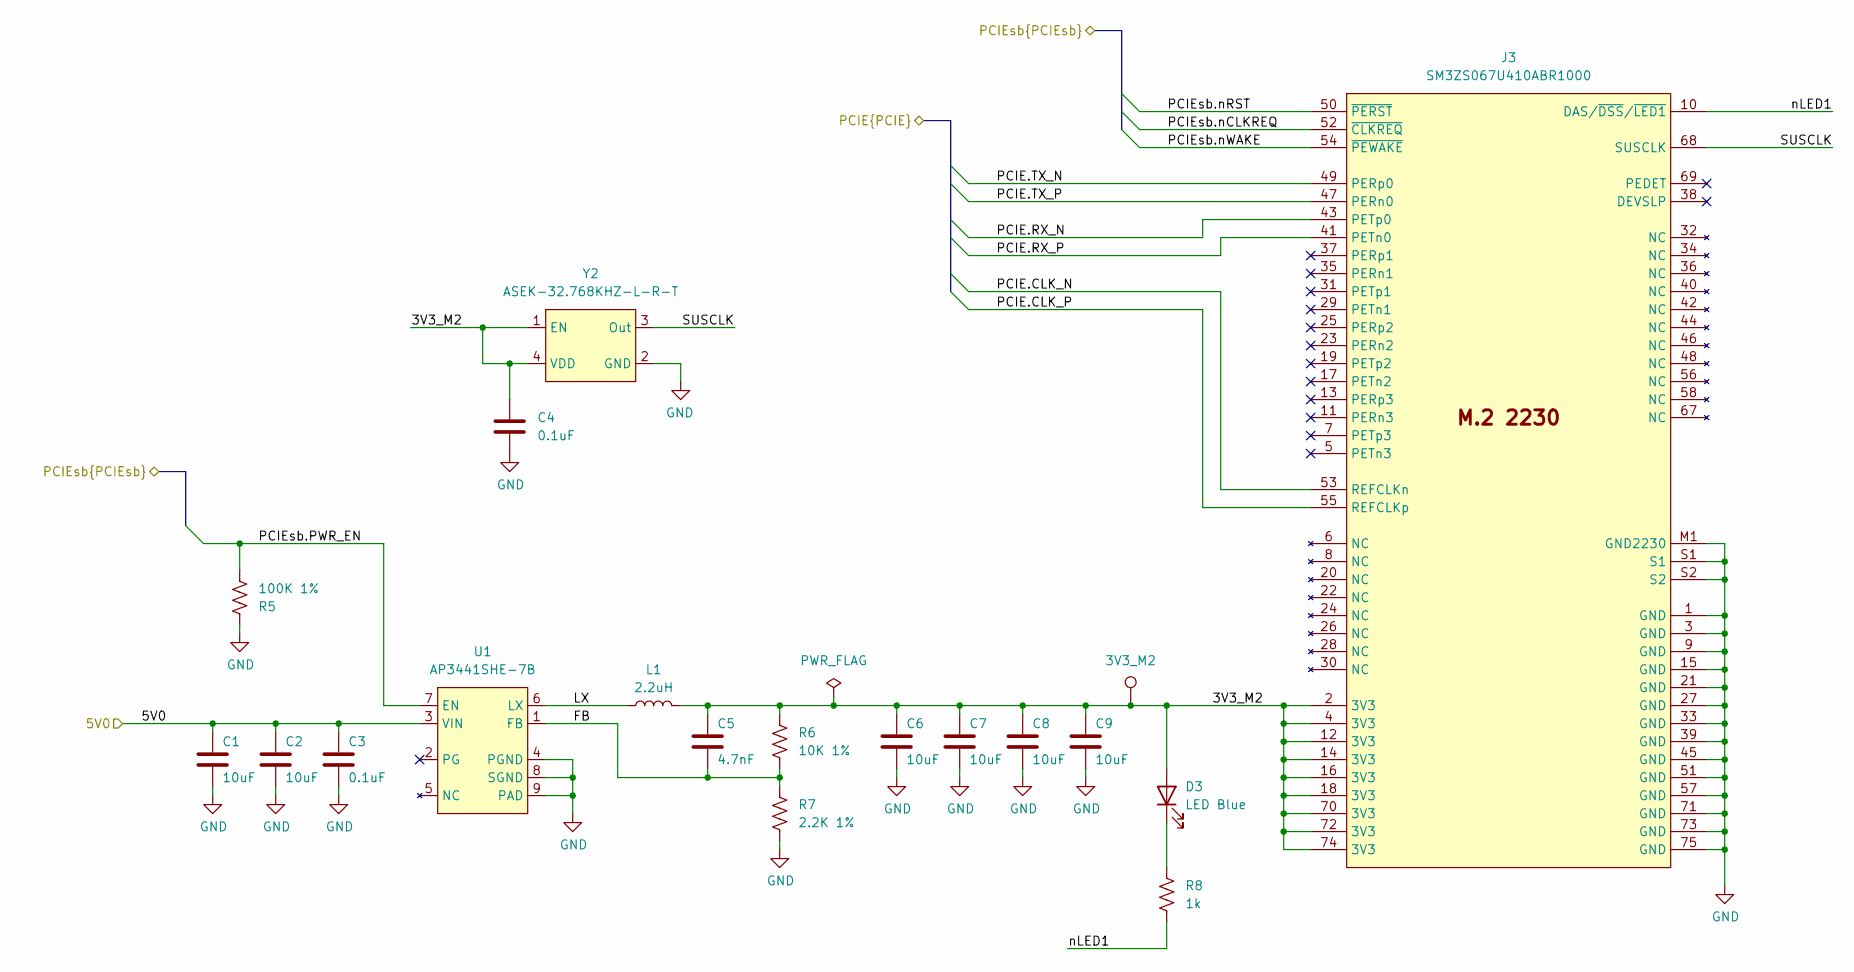
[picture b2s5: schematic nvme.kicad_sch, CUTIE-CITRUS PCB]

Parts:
3V3_M2: TestPoint; TestPoint_Pad_D1.0mm
C1, C2, C6, C7, C8, C9: 10uF; C_0805_2012Metric
C3, C4: 0.1uF; C_0402_1005Metric
C5: 4.7nF; C_0402_1005Metric
D3: LED Blue; LED_0603_1608Metric
J3: SM3ZS067U410ABR1000; 2230m2
L1: 2.2uH; L_Vishay_IHLP-1616
R5: 100K 1%; R_0402_1005Metric
R6: 10K 1%; R_0402_1005Metric
R7: 2.2K 1%; R_0402_1005Metric
R8: 1k; R_0402_1005Metric
U1: AP3441SHE-7B; DFN-8-1EP_2x2mm_P0.5mm_EP1.05x1.75mm
Y2: ASEK-32.768KHZ-L-R-T; Crystal_SMD_3225-4Pin_3.2x2.5mm

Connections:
/Backplane Connector/5V0: C1.1, C2.1, C3.1, U1.3 (VIN); also elsewhere on the board
/CM5/PCIE.CLK_N: J3.53 (REFCLKn); also elsewhere on the board
/CM5/PCIE.CLK_P: J3.55 (REFCLKp); also elsewhere on the board
/CM5/PCIE.RX_N: J3.43 (PETp0); also elsewhere on the board
/CM5/PCIE.RX_P: J3.41 (PETn0); also elsewhere on the board
/CM5/PCIE.TX_N: J3.49 (PERp0); also elsewhere on the board
/CM5/PCIE.TX_P: J3.47 (PERn0); also elsewhere on the board
/CM5/PCIEsb.PWR_EN: R5.1, U1.7 (EN); also elsewhere on the board
/CM5/PCIEsb.nCLKREQ: J3.52 (~CLKREQ); also elsewhere on the board
/CM5/PCIEsb.nRST: J3.50 (~PERST); also elsewhere on the board
/CM5/PCIEsb.nWAKE: J3.54 (~PEWAKE); also elsewhere on the board
/NVME/3V3_M2: 3V3_M2.1, C4.1, C5.1, C6.1, C7.1, C8.1, C9.1, D3.2 (A), J3.2 (3V3), J3.4 (3V3), J3.12 (3V3), J3.14 (3V3), J3.16 (3V3), J3.18 (3V3), J3.70 (3V3), J3.72 (3V3), J3.74 (3V3), L1.2, R6.1, Y2.1 (EN), Y2.4 (VDD)
/NVME/FB: C5.2, R6.2, R7.1, U1.1 (FB)
/NVME/LX: L1.1, U1.6 (LX)
/NVME/SUSCLK: J3.68 (SUSCLK), Y2.3 (Out)
/NVME/nLED1: J3.10 (DAS/~DSS/~LED1), R8.2
GND: C1.2, C2.2, C3.2, C4.2, C6.2, C7.2, C8.2, C9.2, J3.1 (GND), J3.3 (GND), J3.9 (GND), J3.15 (GND), J3.21 (GND), J3.27 (GND), J3.33 (GND), J3.39 (GND), J3.45 (GND), J3.51 (GND), J3.57 (GND), J3.71 (GND), J3.73 (GND), J3.75 (GND), J3.M1 (GND2230), J3.S1, J3.S2, R5.2, R7.2, U1.4 (PGND), U1.8 (SGND), U1.9 (PAD), Y2.2 (GND); also elsewhere on the board
unnamed: D3.1 (K), R8.1

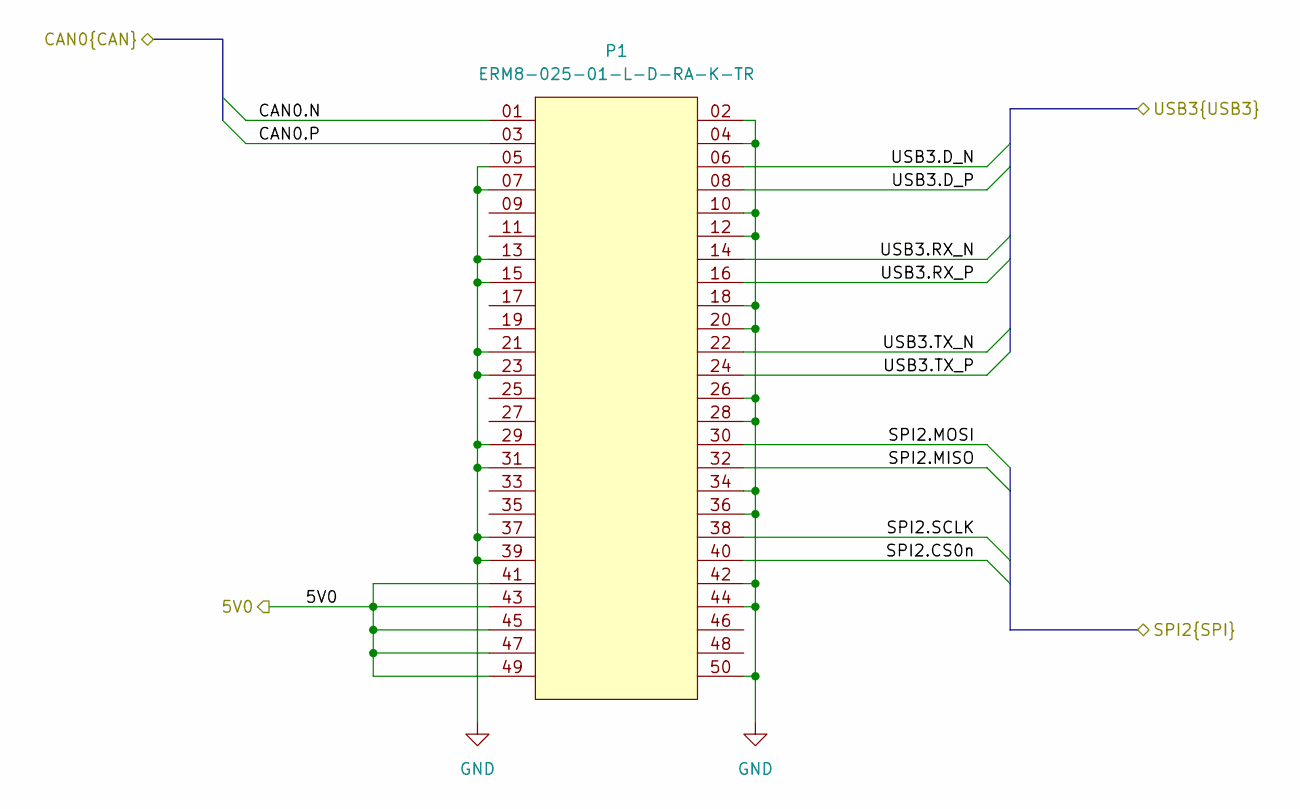
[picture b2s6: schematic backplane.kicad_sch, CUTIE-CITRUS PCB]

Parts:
P1: ERM8-025-01-L-D-RA-K-TR; SAMTEC_ERM8-025-XX-X-D-RA-XX

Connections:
/Backplane Connector/5V0: P1.41, P1.43, P1.45, P1.47, P1.49; also elsewhere on the board
/Backplane Connector/CAN0.N: P1.01; also elsewhere on the board
/Backplane Connector/CAN0.P: P1.03; also elsewhere on the board
/Backplane Connector/SPI2.CS0n: P1.40; also elsewhere on the board
/Backplane Connector/SPI2.MISO: P1.32; also elsewhere on the board
/Backplane Connector/SPI2.MOSI: P1.30; also elsewhere on the board
/Backplane Connector/SPI2.SCLK: P1.38; also elsewhere on the board
/Backplane Connector/USB3.D_N: P1.06; also elsewhere on the board
/Backplane Connector/USB3.D_P: P1.08; also elsewhere on the board
/Backplane Connector/USB3.RX_N: P1.14; also elsewhere on the board
/Backplane Connector/USB3.RX_P: P1.16; also elsewhere on the board
/Backplane Connector/USB3.TX_N: P1.22; also elsewhere on the board
/Backplane Connector/USB3.TX_P: P1.24; also elsewhere on the board
GND: P1.02, P1.04, P1.05, P1.07, P1.10, P1.12, P1.13, P1.15, P1.18, P1.20, P1.21, P1.23, P1.26, P1.28, P1.29, P1.31, P1.34, P1.36, P1.37, P1.39, P1.42, P1.44, P1.50; also elsewhere on the board
